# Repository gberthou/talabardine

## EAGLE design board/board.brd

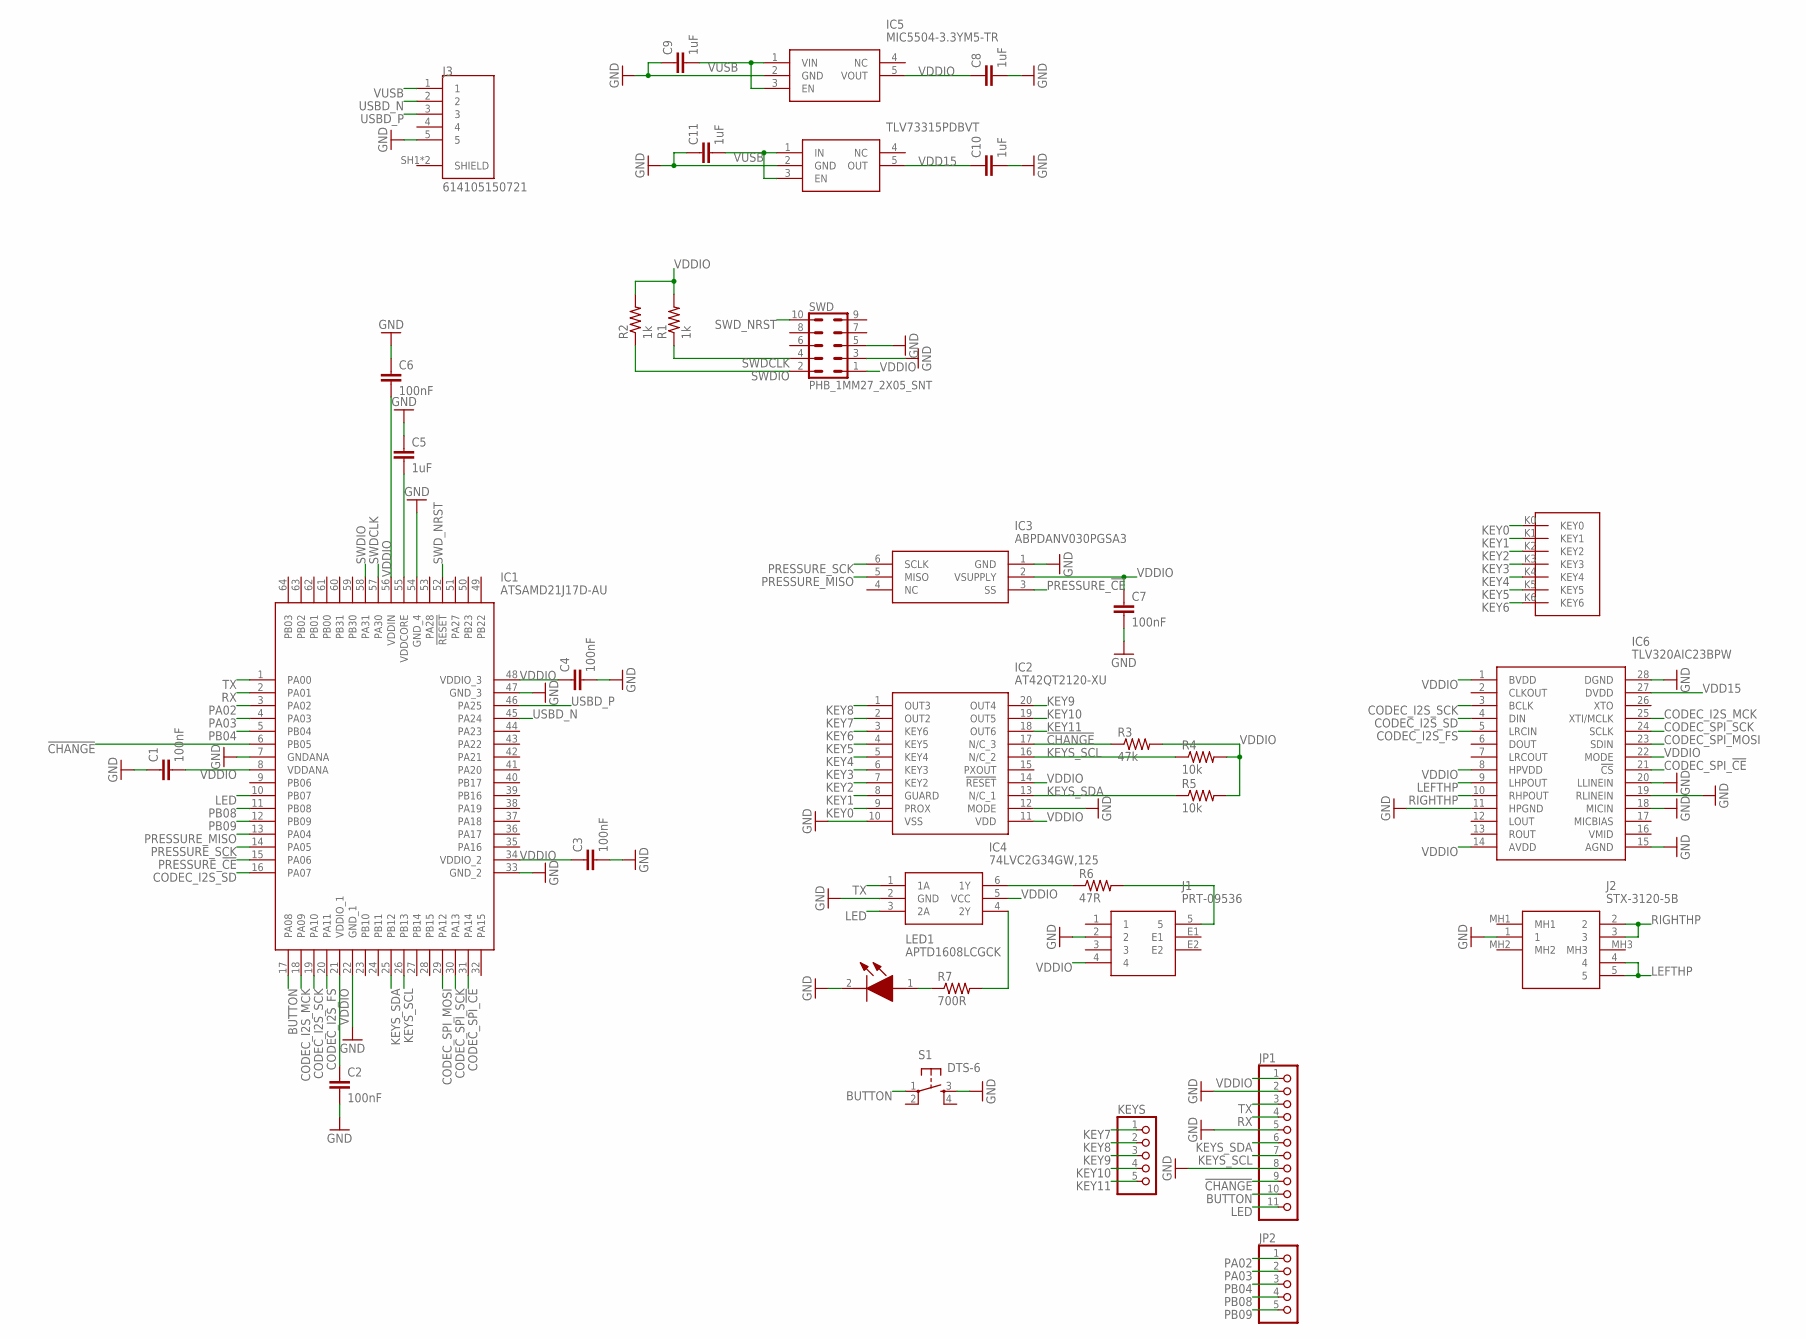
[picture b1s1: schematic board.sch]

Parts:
C1, C2, C3, C4, C6, C7: 100nF; C0603
C5, C8, C9, C10, C11: 1uF; C0603
IC1: ATSAMD21J17D-AU; QFP50P1200X1200X120-64N
IC2: AT42QT2120-XU; SOP65P638X120-20N
IC3: ABPDANV030PGSA3
IC4: 74LVC2G34GW,125; SOP65P210X110-6N
IC5: MIC5504-3.3YM5-TR; SOT95P280X145-5N
IC6: TLV320AIC23BPW; SOP65P640X120-28N
J1: PRT-09536; PRT09536
J2: STX-3120-5B; STX31205B
J3: 614105150721; WURTH_614105150721
JP1: PINHD-1X11; 1X11
JP2: PINHD-1X5; 1X05
KEYS: PINHD-1X5; 1X05
LED1: APTD1608LCGCK; APT1608CGCK
R1, R2: 1k; R0603
R3: 47k; R0603
R4, R5: 10k; R0603
R6: 47R; R0603
R7: 700R; R0603
S1: DTS-6
SWD: PHB_1MM27_2X05_SNT
TLV73315PDBVT: TLV73333PDBVT; SOT95P280X145-5N
U$1: KEYS

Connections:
!CHANGE!: IC1.6 (PB05), IC2.17 (N/C_3), JP1.9, R3.1
BUTTON: IC1.17 (PA08), JP1.10, S1.1
CODEC_I2S_FS: IC1.20 (PA11), IC6.5 (LRCIN)
CODEC_I2S_MCK: IC1.18 (PA09), IC6.25 (XTI/MCLK)
CODEC_I2S_SCK: IC1.19 (PA10), IC6.3 (BCLK)
CODEC_I2S_SD: IC1.16 (PA07), IC6.4 (DIN)
CODEC_SPI_!CE!: IC1.31 (PA14), IC6.21 (!CS)
CODEC_SPI_MOSI: IC1.29 (PA12), IC6.23 (SDIN)
CODEC_SPI_SCK: IC1.30 (PA13), IC6.24 (SCLK)
GND: C1.1, C2.2, C3.2, C4.2, C5.1, C6.1, C7.2, C8.2, C9.1, C10.2, C11.1, IC1.7 (GNDANA), IC1.22 (GND_1), IC1.33 (GND_2), IC1.47 (GND_3), IC1.54 (GND_4), IC2.10 (VSS), IC2.12 (MODE), IC3.1 (GND), IC4.2 (GND), IC5.2 (GND), IC6.11 (HPGND), IC6.15 (AGND), IC6.18 (MICIN), IC6.19 (RLINEIN), IC6.20 (LLINEIN), IC6.28 (DGND), J1.2, J2.1, J3.5, JP1.2, JP1.5, JP1.8, LED1.2 (K), S1.3, SWD.3, SWD.5, TLV73315PDBVT.2 (GND)
KEY0: IC2.9 (PROX), U$1.K0 (KEY0)
KEY1: IC2.8 (GUARD), U$1.K1 (KEY1)
KEY2: IC2.7 (KEY2), U$1.K2 (KEY2)
KEY3: IC2.6 (KEY3), U$1.K3 (KEY3)
KEY4: IC2.5 (KEY4), U$1.K4 (KEY4)
KEY5: IC2.4 (KEY5), U$1.K5 (KEY5)
KEY6: IC2.3 (KEY6), U$1.K6 (KEY6)
KEY7: IC2.2 (OUT2), KEYS.1
KEY8: IC2.1 (OUT3), KEYS.2
KEY9: IC2.20 (OUT4), KEYS.3
KEY10: IC2.19 (OUT5), KEYS.4
KEY11: IC2.18 (OUT6), KEYS.5
KEYS_SCL: IC1.26 (PB13), IC2.16 (N/C_2), JP1.7, R4.1
KEYS_SDA: IC1.25 (PB12), IC2.13 (N/C_1), JP1.6, R5.1
LED: IC1.10 (PB07), IC4.3 (2A), JP1.11
LEFTHP: IC6.9 (LHPOUT), J2.4, J2.5
unnamed: IC4.4 (2Y), R7.2
unnamed: J1.5, R6.2
unnamed: C5.2, IC1.55 (VDDCORE)
unnamed: LED1.1 (A), R7.1
unnamed: IC4.6 (1Y), R6.1
PA02: IC1.3 (PA02), JP2.1
PA03: IC1.4 (PA03), JP2.2
PB04: IC1.5 (PB04), JP2.3
PB08: IC1.11 (PB08), JP2.4
PB09: IC1.12 (PB09), JP2.5
PRESSURE_!CE!: IC1.15 (PA06), IC3.3 (SS)
PRESSURE_MISO: IC1.13 (PA04), IC3.5 (MISO)
PRESSURE_SCK: IC1.14 (PA05), IC3.6 (SCLK)
RIGHTHP: IC6.10 (RHPOUT), J2.2, J2.3
RX: IC1.2 (PA01), JP1.4
SWDCLK: IC1.57 (PA30), R1.1, SWD.4
SWDIO: IC1.58 (PA31), R2.1, SWD.2
SWD_NRST: IC1.52 (!RESET), SWD.10
TX: IC1.1 (PA00), IC4.1 (1A), JP1.3
USBD_N: IC1.45 (PA24), J3.2
USBD_P: IC1.46 (PA25), J3.3
VDD15: C10.1, IC6.27 (DVDD), TLV73315PDBVT.5 (OUT)
VDDIO: C1.2, C2.1, C3.1, C4.1, C6.2, C7.1, C8.1, IC1.8 (VDDANA), IC1.21 (VDDIO_1), IC1.34 (VDDIO_2), IC1.48 (VDDIO_3), IC1.56 (VDDIN), IC2.11 (VDD), IC2.14 (!RESET), IC3.2 (VSUPPLY), IC4.5 (VCC), IC5.5 (VOUT), IC6.1 (BVDD), IC6.8 (HPVDD), IC6.14 (AVDD), IC6.22 (MODE), J1.4, JP1.1, R1.2, R2.2, R3.2, R4.2, R5.2, SWD.1
VUSB: C9.2, C11.2, IC5.1 (VIN), IC5.3 (EN), J3.1, TLV73315PDBVT.1 (IN), TLV73315PDBVT.3 (EN)

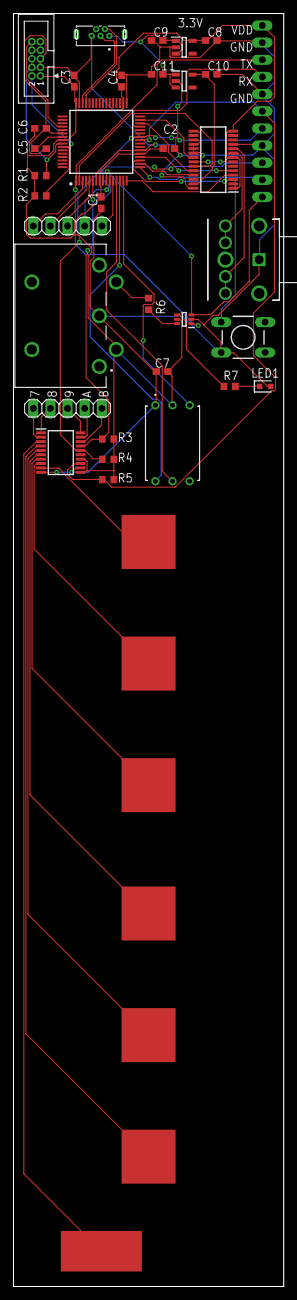
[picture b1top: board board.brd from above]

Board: 2 copper layers, 40.0 x 188.5 mm, 35 parts (1 on the bottom side), 50 nets.

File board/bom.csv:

"Part","Value","Device","Package","Description","ARROW_PART_NUMBER","ARROW_PRICE-STOCK","AVAILABILITY","DESCRIPTION","HEIGHT","MANUFACTURER_NAME","MANUFACTURER_PART_NUMBER","MF","MOUSER_PART_NUMBER","MOUSER_PRICE-STOCK","MP","PACKAGE","POPULARITY","PRICE","PURCHASE-URL","SPICEPREFIX",
"C1","100nF","C-EUC0603","C0603","CAPACITOR, European symbol","","","","","","","","","","","","","73","","","C",
"C2","100nF","C-EUC0603","C0603","CAPACITOR, European symbol","","","","","","","","","","","","","73","","","C",
"C3","100nF","C-EUC0603","C0603","CAPACITOR, European symbol","","","","","","","","","","","","","73","","","C",
"C4","100nF","C-EUC0603","C0603","CAPACITOR, European symbol","","","","","","","","","","","","","73","","","C",
"C5","1uF","C-EUC0603","C0603","CAPACITOR, European symbol","","","","","","","","","","","","","73","","","C",
"C6","100nF","C-EUC0603","C0603","CAPACITOR, European symbol","","","","","","","","","","","","","73","","","C",
"C7","100nF","C-EUC0603","C0603","CAPACITOR, European symbol","","","","","","","","","","","","","73","","","C",
"C8","1uF","C-EUC0603","C0603","CAPACITOR, European symbol","","","","","","","","","","","","","73","","","C",
"C9","1uF","C-EUC0603","C0603","CAPACITOR, European symbol","","","","","","","","","","","","","73","","","C",
"C10","1uF","C-EUC0603","C0603","CAPACITOR, European symbol","","","","","","","","","","","","","73","","","C",
"C11","1uF","C-EUC0603","C0603","CAPACITOR, European symbol","","","","","","","","","","","","","73","","","C",
"IC1","ATSAMD21J17D-AU","ATSAMD21J17D-AU","QFP50P1200X1200X120-64N","64TQFP IND TEMP, GREEN,1.6-3.6V,48MHz","ATSAMD21J17D-AU","https://www.arrow.com/en/products/atsamd21j17d-au/microchip-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","","64TQFP IND TEMP, GREEN,1.6-3.6V,48MHz","1.2mm","Microchip","ATSAMD21J17D-AU","","556-ATSAMD21J17D-AU","https://www.mouser.co.uk/ProductDetail/Microchip-Technology-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","","","","","","",
"IC2","AT42QT2120-XU","AT42QT2120-XU","SOP65P638X120-20N","Capacitive Touch Sensors  12 channel AT42QT2120-XU, Spread-Spectrum Charge-Transfer Touch Screen Controller Serial-I2C, 20-Pin TSSOP","AT42QT2120-XU","https://www.arrow.com/en/products/at42qt2120-xu/microchip-te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","","Capacitive Touch Sensors  12 channel AT42QT2120-XU, Spread-Spectrum Charge-Transfer Touch Screen Controller Serial-I2C, 20-Pin TSSOP","1.2mm","Microchip","AT42QT2120-XU","","556-AT42QT2120-XU","https://www.mouser.co.uk/ProductDetail/Microchip-Technology-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","","","","","","",
"IC3","ABPDANV030PGSA3","ABPDANV030PGSA3","ABPDANV030PGSA3","Sensor: pressure, Range:030psi, gage, Output conf: SPI, Case: DIP","","","","Sensor: pressure"," Range:030psi"," gage"," Output conf: SPI"," Case: DIP","10.63mm","Honeywell","ABPDANV030PGSA3","","785-ABPDANV030PGSA3","https://www.mouser.co.uk/ProductDetail/Honeywell/ABPDANV030P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","","",
"IC4","74LVC2G34GW,125","74LVC2G34GW,125","SOP65P210X110-6N","74LVC2G34 - Dual buffer gate@en-us","74LVC2G34GW,125","https://www.arrow.com/en/products/74lvc2g34gw125/nexperia","","74LVC2G34 - Dual buffer gate@en-us","1.1mm","Nexperia","74LVC2G34GW,125","","771-LVC2G34GW125","https://www.mouser.co.uk/ProductDetail/Nexperia/74LVC2G34GW1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","","","","","","",
"IC5","MIC5504-3.3YM5-TR","MIC5504-3.3YM5-TR","SOT95P280X145-5N","MICROCHIP - MIC5504-3.3YM5-TR - LDO VOLT REG, 0.3A, 3.3V, SOT-23-5","MIC5504-3.3YM5-TR","https://www.arrow.com/en/products/mic5504-3.3ym5-tr/microchi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","","MICROCHIP - MIC5504-3.3YM5-TR - LDO VOLT REG, 0.3A, 3.3V, SOT-23-5","1.45mm","Microchip","MIC5504-3.3YM5-TR","","998-MIC5504-3.3YM5TR","https://www.mouser.co.uk/ProductDetail/Microchip-Technology-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","","","","","","",
"IC6","TLV320AIC23BPW","TLV320AIC23BPW","SOP65P640X120-28N","TLV320AIC23BPWG4, Audio Codec 2 (ADC), 2 (DAC)-channel 32bit- 96ksps Serial-SPI 28-Pin TSSOP","TLV320AIC23BPW","https://www.arrow.com/en/products/tlv320aic23bpw/texas-instruments","","TLV320AIC23BPWG4, Audio Codec 2 (ADC), 2 (DAC)-channel 32bit- 96ksps Serial-SPI 28-Pin TSSOP","1.2mm","Texas Instruments","TLV320AIC23BPW","","595-TLV320AIC23BPW","https://www.mouser.co.uk/ProductDetail/Texas-Instruments/TLV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","","","","","","",
"J1","PRT-09536","PRT-09536","PRT09536","SparkFun Accessories MIDI Connector - Female Right Angle","","","","SparkFun Accessories MIDI Connector - Female Right Angle","19.5mm","SparkFun","PRT-09536","","474-PRT-09536","https://www.mouser.co.uk/ProductDetail/SparkFun/PRT-09536?qs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","","","","","","",
"J2","STX-3120-5B","STX-3120-5B","STX31205B","KYCON - STX-3120-5B - STEREO JACK, 3.5MM, 5POS, PBT GF, PCB","","","","KYCON - STX-3120-5B - STEREO JACK, 3.5MM, 5POS, PBT GF, PCB","10mm","Kycon","STX-3120-5B","","806-STX-3120-5B","https://www.mouser.co.uk/ProductDetail/Kycon/STX-3120-5B/?qs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","","","","","","",
"J3","614105150721","614105150721","WURTH_614105150721","Vertical Through Hole, sion 2.0 Micro USB Connector Socket Check prices","","","Warning"," USB - micro B USB 2.0 Receptacle Connector 5 Position Through Hole ","","","","Würth Elektronik","","","614105150721","None","","None","https://pricing.snapeda.com/search/part/614105150721/?ref=eda","",
"JP1","","PINHD-1X11","1X11","PIN HEADER","","","","","","","","","","","","","12","","","",
"JP2","","PINHD-1X5","1X05","PIN HEADER","","","","","","","","","","","","","69","","","",
"KEYS","","PINHD-1X5","1X05","PIN HEADER","","","","","","","","","","","","","69","","","",
"LED1","APTD1608LCGCK","APTD1608LCGCK","APT1608CGCK","Standard LEDs - SMD 0603 Dome Lens LED Green- 570nm","","","","Standard LEDs - SMD 0603 Dome Lens LED Green- 570nm","mm","Kingbright","APTD1608LCGCK","","604-APTD1608LCGCK","https://www.mouser.co.uk/ProductDetail/Kingbright/APTD1608LC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","","","","","","",
"R1","1k","R-US_R0603","R0603","RESISTOR, American symbol","","","","","","","","","","","","","77","","","R",
"R2","1k","R-US_R0603","R0603","RESISTOR, American symbol","","","","","","","","","","","","","77","","","R",
"R3","47k","R-US_R0603","R0603","RESISTOR, American symbol","","","","","","","","","","","","","77","","","R",
"R4","10k","R-US_R0603","R0603","RESISTOR, American symbol","","","","","","","","","","","","","77","","","R",
"R5","10k","R-US_R0603","R0603","RESISTOR, American symbol","","","","","","","","","","","","","77","","","R",
"R6","47R","R-US_R0603","R0603","RESISTOR, American symbol","","","","","","","","","","","","","77","","","R",
"R7","700R","R-US_R0603","R0603","RESISTOR, American symbol","","","","","","","","","","","","","77","","","R",
"S1","DTS-6","DTS-6","DTS-6","","","","","","","","","","","","","","","","","",
"SWD","PHB_1MM27_2X05_SNT","PHB_1MM27_2X05_SNT","PHB_1MM27_2X05_SNT","Pin Header Box-Type, 1.27mm/0.5"/50mil Pitch, 2x05 Circuits","","","","","","","","","","","","","","","","",
"TLV73315PDBVT","TLV73333PDBVT","TLV73333PDBVT","SOT95P280X145-5N","Capacitor-free 300-mA low-dropout (LDO) regulator with foldback current limit for portable devices","TLV73333PDBVT","https://www.arrow.com/en/products/tlv73333pdbvt/texas-instruments","","Capacitor-free 300-mA low-dropout (LDO) regulator with foldback current limit for portable devices","1.45mm","Texas Instruments","TLV73333PDBVT","","595-TLV73333PDBVT","https://www.mouser.co.uk/ProductDetail/Texas-Instruments/TLV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","","","","","","",
"U$1","KEYS","KEYS","KEYS","","","","","","","","","","","","","","","","","",

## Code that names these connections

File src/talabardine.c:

#include "config.h"
#include "gclk.h"
#include "gpio.h"
#include "pm.h"
#include "sysctrl.h"
#include "sercom.h"
#include "atqt2120.h"
#include "abp-spi.h"
#include "nvic.h"
#include "eic.h"
#include "interrupt.h"
#include "tc.h"
#include "nvmctrl.h"
#include "midi.h"
#include "udc.h"
#include "usb.h"
#include "usb_midi.h"
#include "usb_talabardine.h"
#include "utils.h"

#define EIC_KEYCHANGE 5

#define PRESSURE_OCT1 ABP_PA_2_COUNTS(2000)
#define PRESSURE_OCT2 ABP_PA_2_COUNTS(4000)

#define OCTAVE_OFFSET 4

/*
 * Pin mapping:
 *     # USART (SERCOM 1)
 *         PA00 = TX
 *         PA01 = RX
 *     # Codec (SERCOM 0) // TODO
 *         PA08 = MISO
 *         PA09 = /CE
 *         PA10 = MOSI
 *         PA11 = SCK
 *     # Pressure (SERCOM 0)
 *         PA04 = MISO
 *         PA05 = SCK
 *         PA06 = /CE
 *     # Keys (SERCOM 4)
 *         PB12 = SDA
 *         PB13 = SCL
 *         PB05 = /CHANGE
 *     # LEDs
 *         PB07
 */

// KEY_DRTHR must be high enough so that keys are not triggered from the backside of the PCB
#define KEY_DTHR 64
const struct atqt2120_t keys_config = {
    .keys = {
        {.ctrl.bits = {.en = 0, .gpo = 0, .aks = 0, .guard = 0}, .dthr = KEY_DTHR},
        {.ctrl.bits = {.en = 0, .gpo = 0, .aks = 0, .guard = 0}, .dthr = KEY_DTHR},
        {.ctrl.bits = {.en = 0, .gpo = 0, .aks = 0, .guard = 0}, .dthr = KEY_DTHR},
        {.ctrl.bits = {.en = 0, .gpo = 0, .aks = 0, .guard = 0}, .dthr = KEY_DTHR},
        {.ctrl.bits = {.en = 0, .gpo = 0, .aks = 0, .guard = 0}, .dthr = KEY_DTHR},
        {.ctrl.bits = {.en = 0, .gpo = 0, .aks = 0, .guard = 0}, .dthr = KEY_DTHR},
        {.ctrl.bits = {.en = 0, .gpo = 0, .aks = 0, .guard = 0}, .dthr = KEY_DTHR},
        {.ctrl.bits = {.en = 1, .gpo = 0, .aks = 0, .guard = 0}, .dthr = KEY_DTHR},
        {.ctrl.bits = {.en = 1, .gpo = 0, .aks = 0, .guard = 0}, .dthr = KEY_DTHR},
        {.ctrl.bits = {.en = 1, .gpo = 0, .aks = 0, .guard = 0}, .dthr = KEY_DTHR},
        {.ctrl.bits = {.en = 1, .gpo = 0, .aks = 0, .guard = 0}, .dthr = KEY_DTHR},
        {.ctrl.bits = {.en = 1, .gpo = 0, .aks = 0, .guard = 0}, .dthr = KEY_DTHR}
    },
    .change_port = GPIO_PORT_B,
    .change_pin = 5,
    .di = 1
};

static int keys_to_note(uint8_t keys, unsigned int *octave_modifier)
{
    switch(keys & 0x7f)
    {
        case 0x00:
        case 0x40:
            *octave_modifier = 0;
            return MIDI_NOTE_A;
        case 0x01:
        case 0x41:
            *octave_modifier = 0;
            return MIDI_NOTE_G;
        case 0x02:
        case 0x06:
        case 0x42:
        case 0x46:
            *octave_modifier = 0;
            return MIDI_NOTE_GS;
        case 0x03:
        case 0x43:
            *octave_modifier = 0;
            return MIDI_NOTE_F;
        case 0x07:
        case 0x47:
            *octave_modifier = 0;
            return MIDI_NOTE_DS;
        case 0x0f:
            *octave_modifier = 0;
            return MIDI_NOTE_D;
        case 0x1f:
            *octave_modifier = 0;
            return MIDI_NOTE_C;
        case 0x3e:
        case 0x7e:
            *octave_modifier = 0;
            return MIDI_NOTE_AS;
        case 0x3f:
            *octave_modifier = -1;
            return MIDI_NOTE_AS;
        case 0x7f:
            *octave_modifier = -1;
            return MIDI_NOTE_A;
        default:
            *octave_modifier = 0;
            return -1;
    }
}

static int note_to_midi_key(int note, unsigned int octave)
{
    return MIDI_NOTE_TO_KEY(note, OCTAVE_OFFSET - 1 + octave);
}

static void replace_note(int note)
{
    static int current_note = -1;
    //uint8_t command[7];

    // If nothing to replace... skip
    if(note == current_note)
        return;

    //uint8_t *ptr;
    // 1. Mute the former note, if any
    if(current_note != -1)
    {
        //ptr = midi_note_off(command, 0, current_note, 64);
        usb_midi_note_off(0, note, 64);
    }
    //else
    //    ptr = command;

    // 2. Play the new note, if any
    if(note != -1)
    {
        //ptr = midi_note_on(ptr, 0, note, 64);
        usb_midi_note_on(0, note, 64);
    }

    // 3. Finalize string
    //*ptr = 0;

    // 4. Send command
    //sercom_usart_puts(SERCOM_MIDI, (char*) command);

    // 5. Update current_note
    current_note = note;
}

static void talabardine_init_gpios(void)
{
    // Codec (SERCOM 0)
    //gpio_configure_function(GPIO_PORT_A, 8, GPIO_FUNC_C);
    //gpio_configure_function(GPIO_PORT_A, 9, GPIO_FUNC_C);
    //gpio_configure_function(GPIO_PORT_A, 10, GPIO_FUNC_C);
    //gpio_configure_function(GPIO_PORT_A, 11, GPIO_FUNC_C);

    // USART (SERCOM 1)
    gpio_configure_function(GPIO_PORT_A, 0, GPIO_FUNC_D);
    gpio_configure_function(GPIO_PORT_A, 1, GPIO_FUNC_D);

    // Pressure (SERCOM 0)
    gpio_configure_function(GPIO_PORT_A, 4, GPIO_FUNC_D);
    gpio_configure_function(GPIO_PORT_A, 5, GPIO_FUNC_D);
    gpio_configure_io      (GPIO_PORT_A, 6, true); // /CE must be manual because of SPI bursts
    gpio_set_output        (GPIO_PORT_A, 6, true);

    // Keys (SERCOM 4)
    gpio_configure_function(GPIO_PORT_B, 12, GPIO_FUNC_C);
    gpio_configure_function(GPIO_PORT_B, 13, GPIO_FUNC_C);
    // /CHANGE signal is handled by atqt2120_init

    // LED
    gpio_configure_io(GPIO_PORT_B, 7, true);
    gpio_set_output(GPIO_PORT_B, 7, false);

    // Button
    gpio_configure_io(GPIO_PORT_A, 8, false);
    gpio_enable_pull(GPIO_PORT_A, 8, true);

    // USB
    gpio_configure_function(GPIO_PORT_A, 24, GPIO_FUNC_G);
    gpio_configure_function(GPIO_PORT_A, 25, GPIO_FUNC_G);
}

static void talabardine_init_sercoms(void)
{
    sercom_init_usart(SERCOM_MIDI_CHANNEL, USART_TXPO_PAD0, USART_RXPO_DISABLE, /*31250*/ 115200);
    sercom_init_spi_master(SERCOM_PRESSURE_CHANNEL, SPI_OUT_PAD312, SPI_IN_PAD0, 800000);
    sercom_init_i2c_master(SERCOM_KEYS_CHANNEL, 400000);
}

static uint8_t keys;
static uint8_t octave;

void talabardine_init(void)
{
    sysctrl_init_DFLL48M();

    // 37.12: NVM needs at least 1 wait state @48MHz when Vcc > 2.7v
    nvmctrl_set_wait_states(1);
    gclk_set_frequency(GCLK0, 48000000); // Main clock @48MHz

    pm_enable_APB_clock(PM_CLK_SERCOM0, true);
    pm_enable_APB_clock(PM_CLK_SERCOM1, true);
    pm_enable_APB_clock(PM_CLK_SERCOM2, true);
    pm_enable_APB_clock(PM_CLK_SERCOM4, true);
    pm_enable_APB_clock(PM_CLK_TC3, true);

    talabardine_init_gpios();
    talabardine_init_sercoms();
    
    gpio_set_output(GPIO_PORT_B, 7, true);
    sercom_usart_puts(SERCOM_MIDI_CHANNEL, "Press button to start");
    for(size_t i = 0; gpio_read(GPIO_PORT_A, 8); ++i)
    {
        sercom_usart_putc(SERCOM_MIDI_CHANNEL, (i & 1) ? '\b' : '_');
        for(size_t j = 0; j < 5000000; ++j)
            asm volatile("nop");
    }
    gpio_set_output(GPIO_PORT_B, 7, false);
    
    nvic_enable(NVIC_SERCOM0 + SERCOM_KEYS_CHANNEL);
    interrupt_enable();
    atqt2120_init(&keys_config);
    keys = atqt2120_read_status();
    octave = 0;

    /* Normally, EIC has higher (lower value) priority than SERCOM4 (keys), so we have to reverse
     * priority in order, for the key handler, to be able to use interrupt-based I2C.
     * Priority bits 5:0 are ignored so it starts with 64.
     */
    nvic_set_priority(NVIC_EIC, 64);
    eic_init();
    eic_enable(EIC_KEYCHANGE);
    nvic_enable(NVIC_EIC);
    
    tc_init(TC3, GCLK0, 1000);
    nvic_enable(NVIC_TC3);

    usb_talabardine_init();
    usb_midi_init();
    nvic_enable(NVIC_USB);
}

void keychange_handler(void)
{
    static int t = 1;
    
    eic_clear(EIC_KEYCHANGE);
    nvic_clear(NVIC_EIC);
    
    gpio_set_output(GPIO_PORT_B, 7, t);
    t = !t;

    uint8_t new_keys = atqt2120_read_status(); // Reads AND acknowledges the interrupt on the ATQT2120 side
    if(octave > 0) // Was playing
    {
        unsigned int octave_modifier;
        int new_note = keys_to_note(new_keys, &octave_modifier);
        if(new_note >= 0)
            new_note = note_to_midi_key(new_note, octave + octave_modifier);
        else
            dump(&new_keys, 1);
        replace_note(new_note);
    }
    keys = new_keys;
}

void pressure_handler(void)
{
    tc_clear_interrupt(TC3);
    nvic_clear(NVIC_TC3);

    uint16_t new_pressure = abp_wait_until_valid_pressure();
    if(new_pressure >= PRESSURE_OCT1)
    {
        uint8_t new_octave = (new_pressure >= PRESSURE_OCT2 ? 2 : 1);
        if(new_octave != octave)
        {
            unsigned int octave_modifier;
            int new_note = keys_to_note(keys, &octave_modifier);
            new_note = note_to_midi_key(new_note, new_octave + octave_modifier);
            replace_note(new_note);
            octave = new_octave;
        }
    }
    else
    {
        octave = 0;
        replace_note(-1);
    }
}

void sercom4_handler(void) // keys i2c
{
    nvic_clear(NVIC_SERCOM0 + 4);
    sercom_i2c_interrupt(4);
}

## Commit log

2021-04-22 First version, UART and I2C support
2021-04-22 Basic driver for ATQT2120
2021-04-24 Basic driver for ABP series pressure sensor
2021-04-24 Improved key sensor sensitivity and reactivity
2021-04-25 Interrupt-based key detection
2021-04-26 Timer-based interrupts (TC)
2021-04-26 First playable version, as a MIDI controller
2021-12-01 Simple USB driver capable of sending descriptors and reacting upon receiving SET_CONFIGURATION messages
2021-12-04 USB MIDI endpoint descriptors + Set endpoint buffers to 128 bytes
2021-12-15 USB MIDI 1.00 + Compatibility with arm-none-eabi-gcc 6.3.1
2021-12-18 Interrupt-based I2C driver + fixed ATQT2120 driver
2021-12-19 Integration with USB driver + Fixed ATQT2120 driver
2021-12-20 Protocol- and talabardine-specific USB drivers are now separate
